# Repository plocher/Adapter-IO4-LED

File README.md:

# Adapter-IO4-LED
## License: CERN Open Hardware Licence v1.2

RJ12/6 breakout board, for driving LEDs - includes resistor pack

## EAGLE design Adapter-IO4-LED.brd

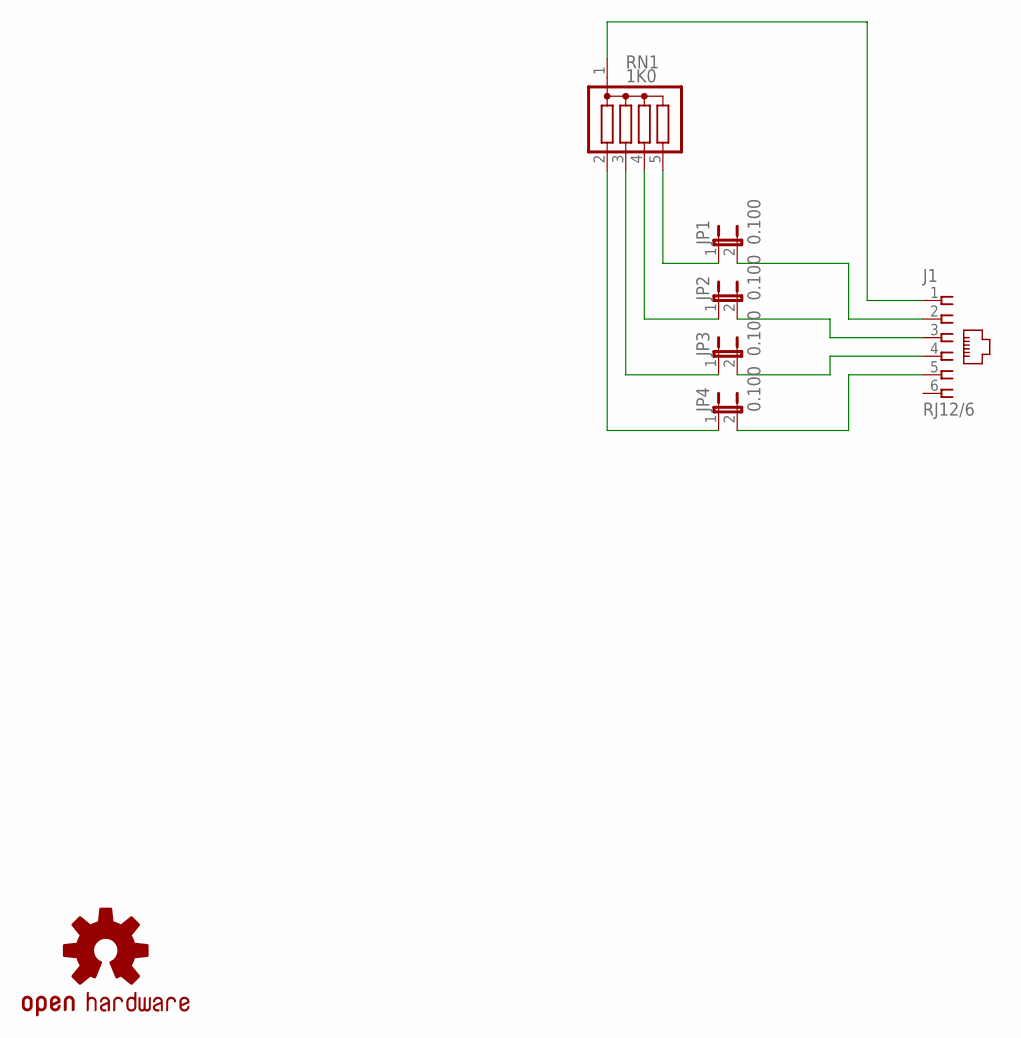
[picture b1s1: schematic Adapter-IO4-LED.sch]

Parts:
J1: RJ12/6; RJ25-PANEL
JP1, JP2, JP3, JP4: 0.100; 1X02_LOCK
RN1: 1K0; SIL5
U$1: OSHW; OSHW-LOGO-M

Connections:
unnamed: JP1.1, RN1.5
unnamed: JP2.1, RN1.4
unnamed: JP3.1, RN1.3
unnamed: JP4.1, RN1.2
unnamed: J1.2, JP1.2
unnamed: J1.3, JP2.2
unnamed: J1.4, JP3.2
unnamed: J1.5, JP4.2
VCC: J1.1, RN1.1

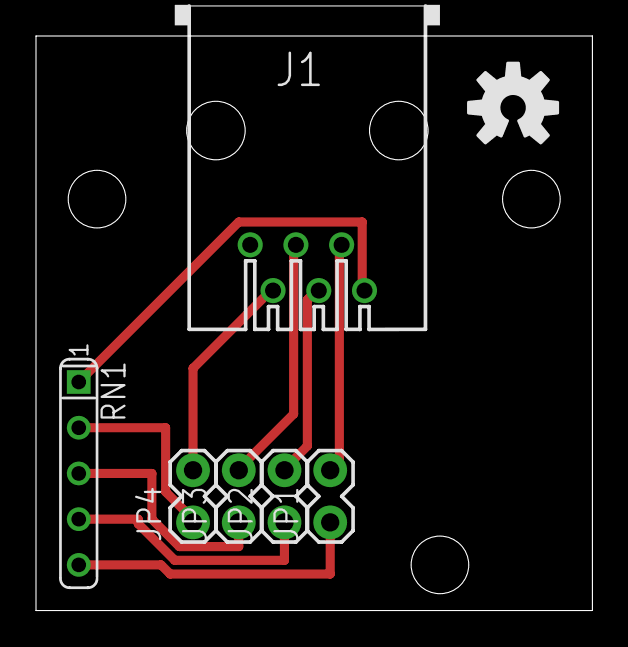
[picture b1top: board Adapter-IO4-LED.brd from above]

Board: 2 copper layers, 30.9 x 31.9 mm, 7 parts (0 on the bottom side), 9 nets.

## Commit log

2019-12-09 added graphic
2020-05-04 updated tags
2020-10-05 added values for connectors
2020-10-06 normalized values

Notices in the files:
parts and their libraries:
SPCoast: http://freedomdefined.org/OSHW Creative Commons - Attribution - ShareAlike 3.0
